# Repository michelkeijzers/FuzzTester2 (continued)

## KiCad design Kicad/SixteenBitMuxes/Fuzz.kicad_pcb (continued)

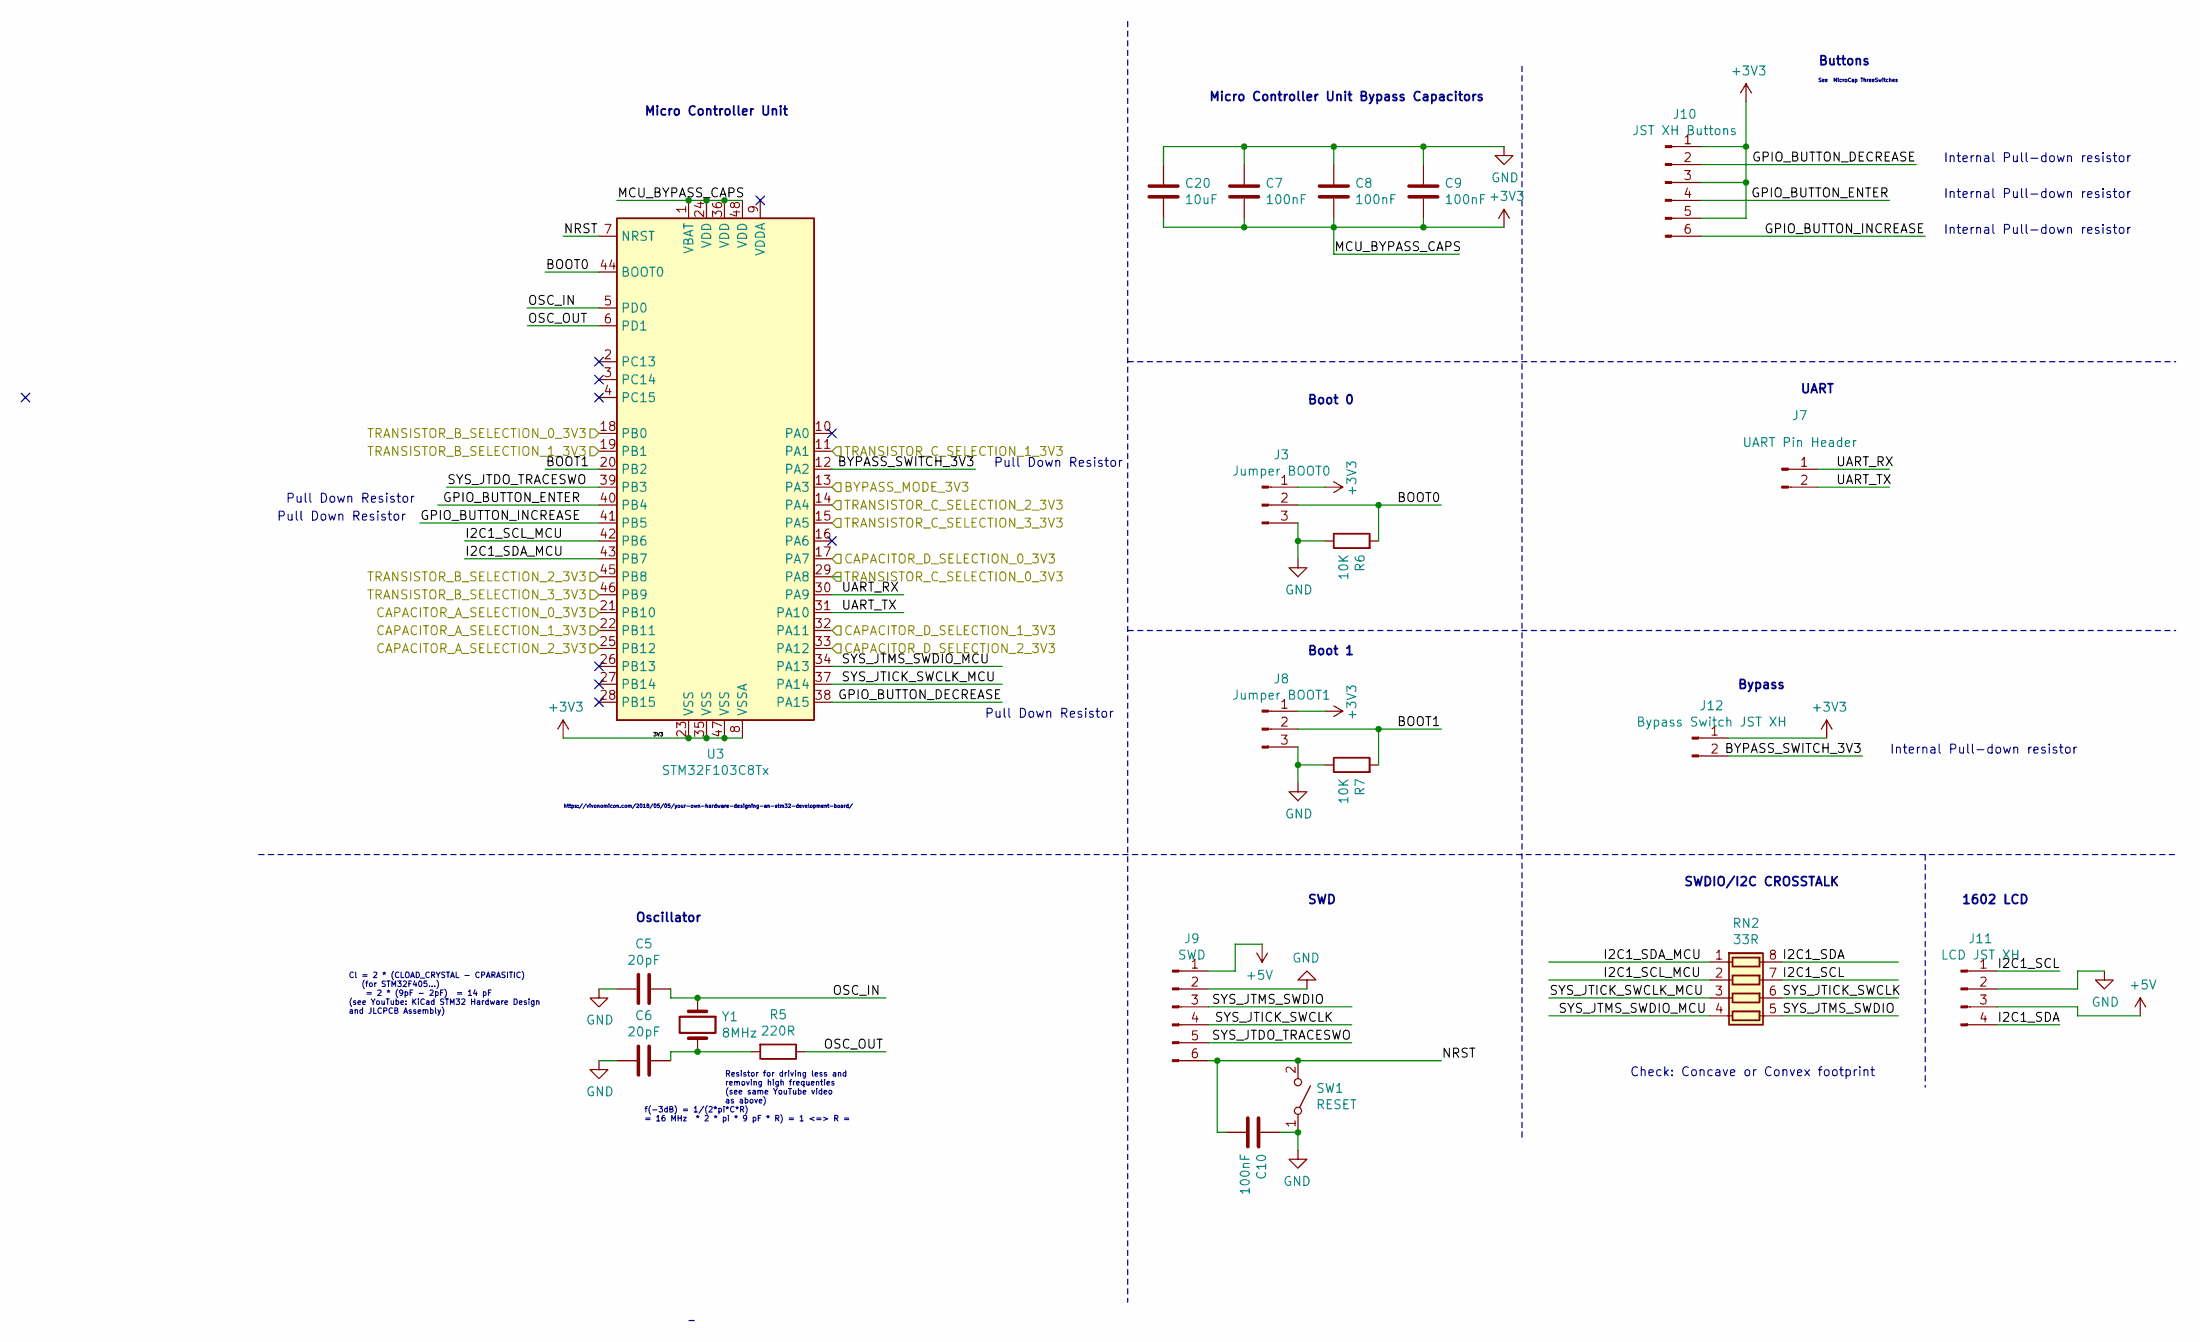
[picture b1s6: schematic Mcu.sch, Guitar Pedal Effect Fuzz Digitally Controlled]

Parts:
C5, C6: 20pF; C_0805_2012Metric_Pad1.15x1.40mm_HandSolder
C7, C8, C9, C10: 100nF; C_0805_2012Metric_Pad1.15x1.40mm_HandSolder
C20: 10uF; C_0805_2012Metric_Pad1.15x1.40mm_HandSolder
J3: Jumper BOOT0; PinHeader_1x03_P2.54mm_Vertical
J7: UART Pin Header; PinHeader_1x02_P2.54mm_Vertical
J8: Jumper BOOT1; PinHeader_1x03_P2.54mm_Vertical
J9: SWD; PinHeader_1x06_P2.54mm_Vertical
J10: JST XH Buttons; JST_XH_B6B-XH-A_1x06_P2.50mm_Vertical
J11: LCD JST XH; JST_XH_B4B-XH-A_1x04_P2.50mm_Vertical
J12: Bypass Switch JST XH; JST_XH_B2B-XH-A_1x02_P2.50mm_Vertical
R5: 220R; R_0805_2012Metric_Pad1.15x1.40mm_HandSolder
R6, R7: 10K; R_0805_2012Metric_Pad1.15x1.40mm_HandSolder
RN2: 33R; R_Array_Convex_4x0603
SW1: RESET; SW_SPST_CK_RS282G05A3
U3: STM32F103C8Tx; LQFP-48_7x7mm_P0.5mm
Y1: 8MHz; Crystal_HC49-4H_Vertical

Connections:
+3V3: C7.2, C8.2, C9.2, C20.2, J3.1, J8.1, J10.1, J10.3, J10.5, J12.1, U3.1 (VBAT), U3.8 (VSSA), U3.23 (VSS), U3.24 (VDD), U3.35 (VSS), U3.36 (VDD), U3.47 (VSS), U3.48 (VDD); also elsewhere on the board
+5V: J9.1, J11.3; also elsewhere on the board
/BYPASS_MODE_3V3: U3.13 (PA3); also elsewhere on the board
/CAPACITOR_A_SELECTION_0_3V3: U3.21 (PB10); also elsewhere on the board
/CAPACITOR_A_SELECTION_1_3V3: U3.22 (PB11); also elsewhere on the board
/CAPACITOR_A_SELECTION_2_3V3: U3.25 (PB12); also elsewhere on the board
/CAPACITOR_D_SELECTION_0_3V3: U3.17 (PA7); also elsewhere on the board
/CAPACITOR_D_SELECTION_1_3V3: U3.32 (PA11); also elsewhere on the board
/CAPACITOR_D_SELECTION_2_3V3: U3.33 (PA12); also elsewhere on the board
/Mcu/BOOT0: J3.2, R6.2, U3.44 (BOOT0)
/Mcu/BOOT1: J8.2, R7.2, U3.20 (PB2)
/Mcu/BYPASS_SWITCH_3V3: J12.2, U3.12 (PA2)
/Mcu/GPIO_BUTTON_DECREASE: J10.2, U3.38 (PA15)
/Mcu/GPIO_BUTTON_ENTER: J10.4, U3.40 (PB4)
/Mcu/GPIO_BUTTON_INCREASE: J10.6, U3.41 (PB5)
/Mcu/I2C1_SCL: J11.1, RN2.7 (R2.2)
/Mcu/I2C1_SCL_MCU: RN2.2 (R2.1), U3.42 (PB6)
/Mcu/I2C1_SDA: J11.4, RN2.8 (R1.2)
/Mcu/I2C1_SDA_MCU: RN2.1 (R1.1), U3.43 (PB7)
/Mcu/NRST: C10.1, J9.6, SW1.2 (B), U3.7 (NRST)
/Mcu/OSC_IN: C5.1, U3.5 (PD0), Y1.1
/Mcu/OSC_OUT: R5.1, U3.6 (PD1)
/Mcu/SYS_JTDO_TRACESWO: J9.5, U3.39 (PB3)
/Mcu/SYS_JTICK_SWCLK: J9.4, RN2.6 (R3.2)
/Mcu/SYS_JTICK_SWCLK_MCU: RN2.3 (R3.1), U3.37 (PA14)
/Mcu/SYS_JTMS_SWDIO: J9.3, RN2.5 (R4.2)
/Mcu/SYS_JTMS_SWDIO_MCU: RN2.4 (R4.1), U3.34 (PA13)
/Mcu/UART_RX: J7.1, U3.30 (PA9)
/Mcu/UART_TX: J7.2, U3.31 (PA10)
/TRANSISTOR_B_SELECTION_0_3V3: U3.18 (PB0); also elsewhere on the board
/TRANSISTOR_B_SELECTION_1_3V3: U3.19 (PB1); also elsewhere on the board
/TRANSISTOR_B_SELECTION_2_3V3: U3.45 (PB8); also elsewhere on the board
/TRANSISTOR_B_SELECTION_3_3V3: U3.46 (PB9); also elsewhere on the board
/TRANSISTOR_C_SELECTION_0_3V3: U3.29 (PA8); also elsewhere on the board
/TRANSISTOR_C_SELECTION_1_3V3: U3.11 (PA1); also elsewhere on the board
/TRANSISTOR_C_SELECTION_2_3V3: U3.14 (PA4); also elsewhere on the board
/TRANSISTOR_C_SELECTION_3_3V3: U3.15 (PA5); also elsewhere on the board
GND: C5.2, C6.2, C7.1, C8.1, C9.1, C10.2, C20.1, J3.3, J8.3, J9.2, J11.2, R6.1, R7.1, SW1.1 (A); also elsewhere on the board
unnamed: C6.1, R5.2, Y1.2

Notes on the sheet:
Micro Controller Unit Bypass Capacitors
https://vivonomicon.com/2018/05/05/your-own-hardware-designing-an-stm32-development-board/
Boot 0
1602 LCD
Pull Down Resistor
SWDIO/I2C CROSSTALK
Check: Concave or Convex footprint
Bypass
See MicroCap ThreeSwitches
Buttons
Internal Pull-down resistor
Cl = 2 * (CLOAD_CRYSTAL - CPARASITIC) (for STM32F405...) = 2 * (9pF - 2pF) = 14 pF (see YouTube: KiCad STM32 Hardware Design and JLCPCB Assembly)
Resistor for driving less and removing high frequenties (see same YouTube video as above)
f(-3dB) = 1/(2*pi*C*R) = 16 MHz * 2 * pi * 9 pF * R) = 1 <=> R =
Oscillator
Micro Controller Unit
Boot 1
SWD
UART

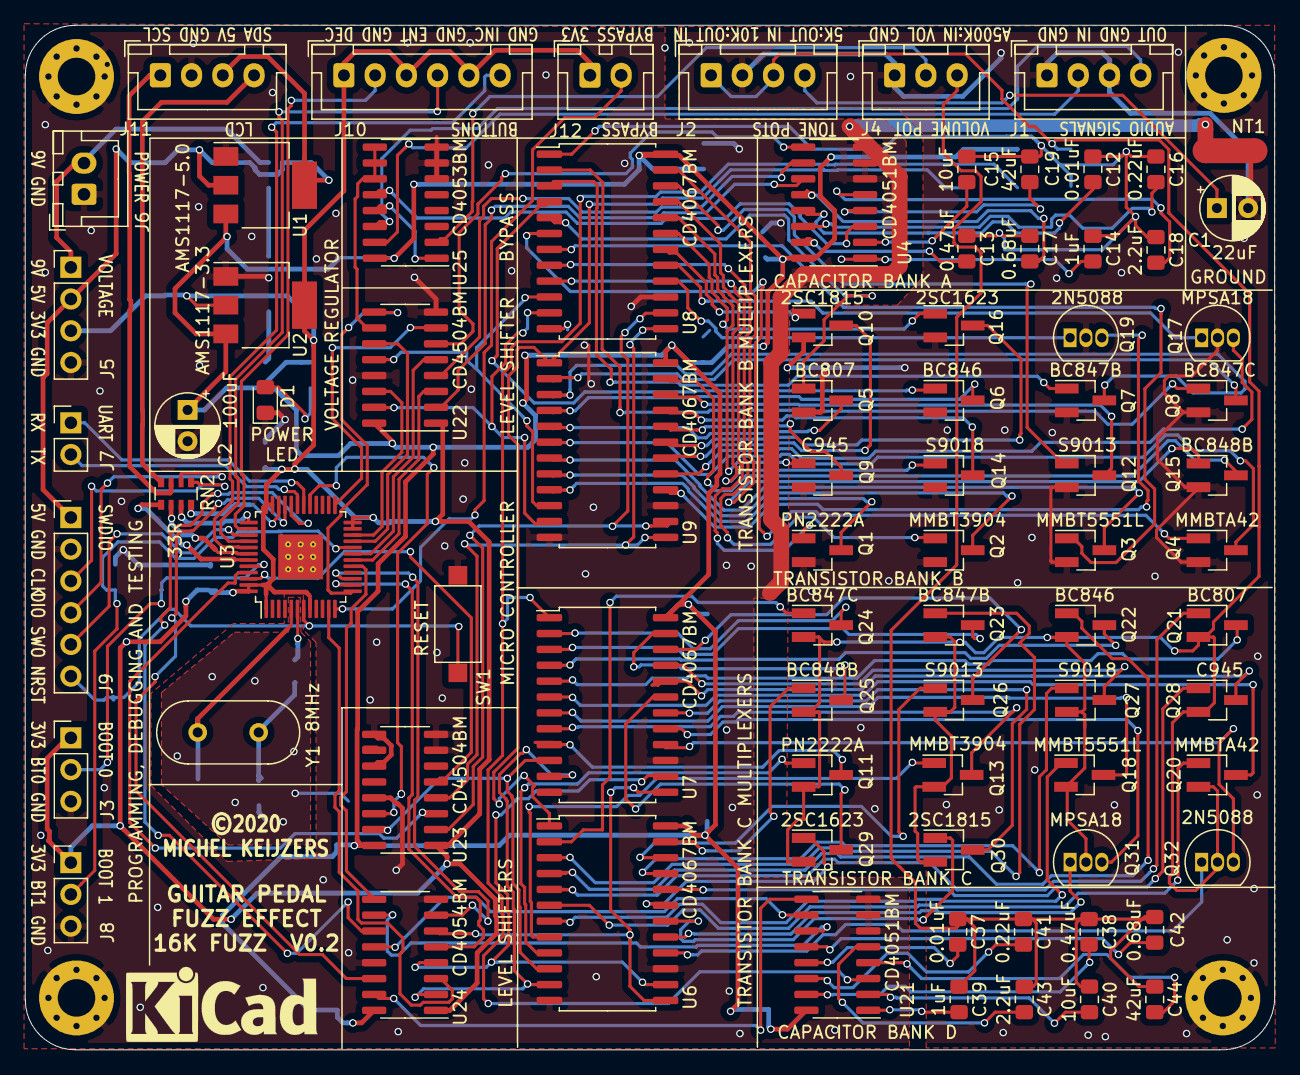
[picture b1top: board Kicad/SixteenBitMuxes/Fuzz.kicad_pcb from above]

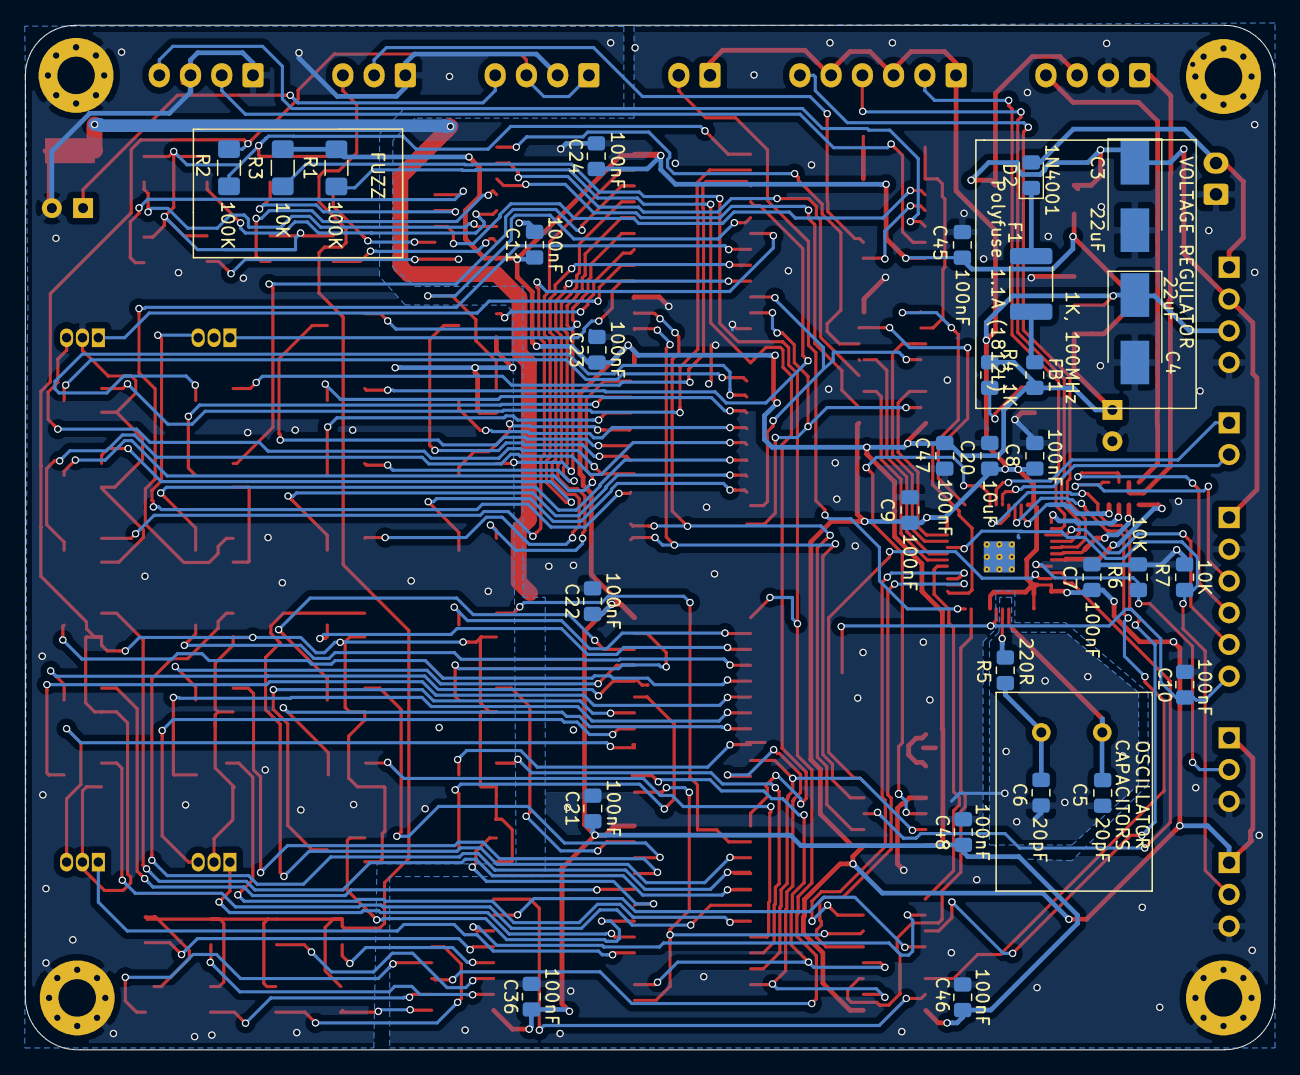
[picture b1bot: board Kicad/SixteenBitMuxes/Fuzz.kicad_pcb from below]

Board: 2 copper layers, 100.0 x 82.0 mm, 113 parts (29 on the bottom side), 151 nets.

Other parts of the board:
Q21: BC807; SOT-23_Handsoldering
Q22: BC846; SOT-23_Handsoldering
Q23: BC847B; SOT-23_Handsoldering
Q29: 2SC1623; SOT-23_Handsoldering
Q32: 2N5088; TO-92_Inline
U21: CD4051BM; SOIC-16_3.9x9.9mm_P1.27mm

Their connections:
/+9V_SAFE: U21.16; also elsewhere on the board
/B10K: Q21.2, Q22.2, Q23.2, Q29.2, Q32.2; also elsewhere on the board
/CAPACITOR_D_SELECTION_0: U21.11; also elsewhere on the board
/CAPACITOR_D_SELECTION_1: U21.10; also elsewhere on the board
/CAPACITOR_D_SELECTION_2: U21.9; also elsewhere on the board
/CapacitorsD/CAPACITOR_AUDIO_INPUT: U21.3; also elsewhere on the board
/TransistorsC/5_BASE: Q21.1; also elsewhere on the board
/TransistorsC/5_COLLECTOR: Q21.3; also elsewhere on the board
/TransistorsC/6_BASE: Q22.1; also elsewhere on the board
/TransistorsC/6_COLLECTOR: Q22.3; also elsewhere on the board
/TransistorsC/7_BASE: Q23.1; also elsewhere on the board
/TransistorsC/7_COLLECTOR: Q23.3; also elsewhere on the board
/TransistorsC/13_BASE: Q29.1; also elsewhere on the board
/TransistorsC/13_COLLECTOR: Q29.3; also elsewhere on the board
/TransistorsC/16_BASE: Q32.1; also elsewhere on the board
/TransistorsC/16_COLLECTOR: Q32.3; also elsewhere on the board
GND: U21.6, U21.7, U21.8; also elsewhere on the board
unnamed 139: U21.13; also elsewhere on the board
unnamed 140: U21.15; also elsewhere on the board
unnamed 141: U21.1; also elsewhere on the board
unnamed 142: U21.2; also elsewhere on the board
unnamed 143: U21.14; also elsewhere on the board
unnamed 144: U21.12; also elsewhere on the board
unnamed 145: U21.5; also elsewhere on the board
unnamed 146: U21.4; also elsewhere on the board

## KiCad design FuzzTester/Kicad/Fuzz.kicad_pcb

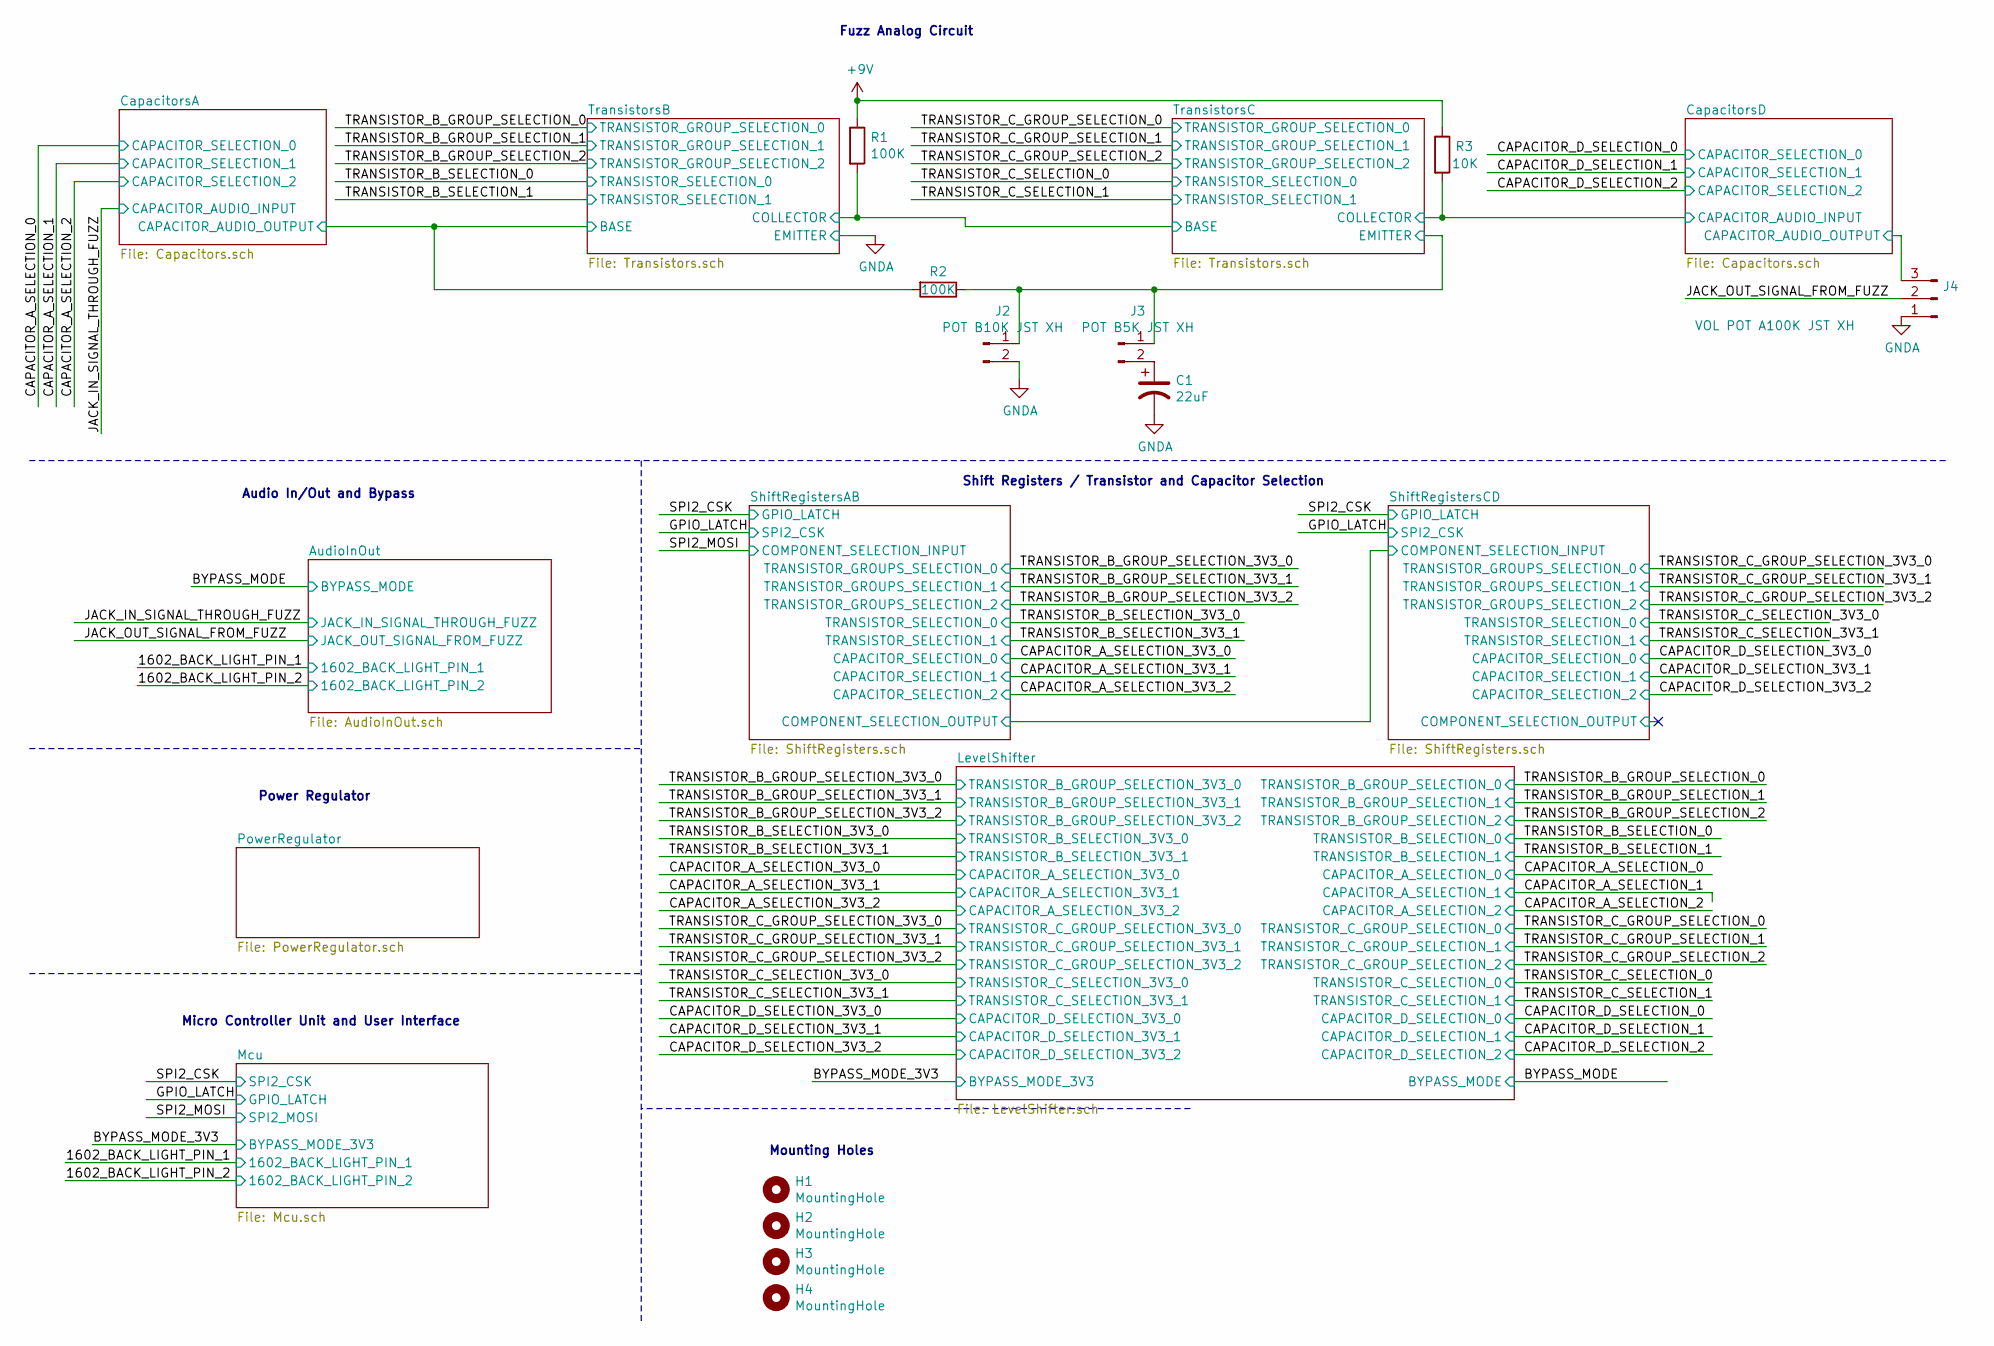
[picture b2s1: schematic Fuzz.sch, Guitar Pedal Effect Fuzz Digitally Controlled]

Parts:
C1: 22uF; CP_Radial_D5.0mm_P2.50mm
H1, H2, H3, H4: MountingHole; MountingHole_3.2mm_M3
J2: POT B10K JST XH; JST_XH_B2B-XH-A_1x02_P2.50mm_Vertical
J3: POT B5K JST XH; JST_XH_B2B-XH-A_1x02_P2.50mm_Vertical
J4: VOL POT A100K JST XH; JST_XH_B3B-XH-A_1x03_P2.50mm_Vertical
R1, R2: 100K; R_1206_3216Metric_Pad1.42x1.75mm_HandSolder
R3: 10K; R_1206_3216Metric_Pad1.42x1.75mm_HandSolder

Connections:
+9V: R1.1, R3.1; also elsewhere on the board
/CapacitorsD/CAPACITOR_AUDIO_INPUT: R3.2; also elsewhere on the board
/CapacitorsD/CAPACITOR_AUDIO_OUTPUT: J4.3; also elsewhere on the board
/JACK_OUT_SIGNAL_FROM_FUZZ: J4.2; also elsewhere on the board
/TransistorsB/BASE: R2.2; also elsewhere on the board
/TransistorsC/BASE: R1.2; also elsewhere on the board
/TransistorsC/EMITTER: J2.1, J3.1, R2.1; also elsewhere on the board
GNDA: C1.2, J2.2, J4.1; also elsewhere on the board
unnamed: C1.1, J3.2

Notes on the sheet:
Fuzz Analog Circuit
Audio In/Out and Bypass
Shift Registers / Transistor and Capacitor Selection
Power Regulator
Micro Controller Unit and User Interface
Mounting Holes

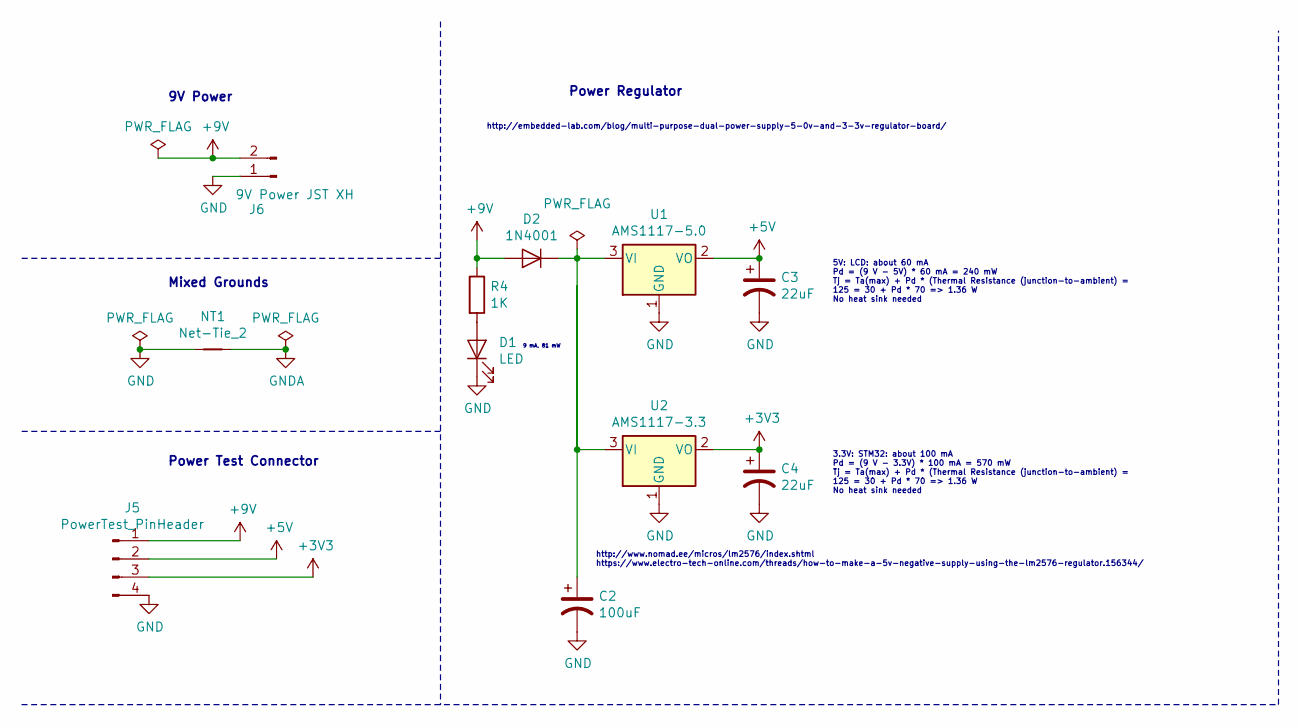
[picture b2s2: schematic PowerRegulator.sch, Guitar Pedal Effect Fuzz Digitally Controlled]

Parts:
C2: 100uF; CP_Radial_D5.0mm_P2.50mm
C3, C4: 22uF; CP_Radial_D5.0mm_P2.50mm
D1: LED; LED_0805_2012Metric_Pad1.15x1.40mm_HandSolder
D2: 1N4001; D_0805_2012Metric_Pad1.15x1.40mm_HandSolder
J5: PowerTest_PinHeader; PinHeader_1x04_P2.54mm_Vertical
J6: 9V Power JST XH; JST_XH_B2B-XH-A_1x02_P2.50mm_Vertical
NT1: Net-Tie_2; NetTie-2_SMD_Pad2.0mm
R4: 1K; R_0805_2012Metric_Pad1.15x1.40mm_HandSolder
U1: AMS1117-5.0; SOT-223-3_TabPin2
U2: AMS1117-3.3; SOT-223-3_TabPin2

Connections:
+3V3: C4.1, J5.3, U2.2 (VO); also elsewhere on the board
+5V: C3.1, J5.2, U1.2 (VO); also elsewhere on the board
+9V: D2.2 (A), J5.1, J6.2, R4.1; also elsewhere on the board
GND: C2.2, C3.2, C4.2, D1.1 (K), J5.4, J6.1, NT1.1, U1.1 (GND), U2.1 (GND); also elsewhere on the board
GNDA: NT1.2; also elsewhere on the board
unnamed: C2.1, D2.1 (K), U1.3 (VI), U2.3 (VI)
unnamed: D1.2 (A), R4.2

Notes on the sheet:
9V Power
9 mA, 81 mW
5V: LCD: about 60 mA Pd = (9 V - 5V) * 60 mA = 240 mW Tj = Ta(max) + Pd * (Thermal Resistance (junction-to-ambient) = 125 = 30 + Pd * 70 => 1.36 W No heat sink needed
3.3V: STM32: about 100 mA Pd = (9 V - 3.3V) * 100 mA = 570 mW Tj = Ta(max) + Pd * (Thermal Resistance (junction-to-ambient) = 125 = 30 + Pd * 70 => 1.36 W No heat sink needed
Power Regulator
http://embedded-lab.com/blog/multi-purpose-dual-power-supply-5-0v-and-3-3v-regulator-board/
https://www.electro-tech-online.com/threads/how-to-make-a-5v-negative-supply-using-the-lm2576-regulator.156344/
http://www.nomad.ee/micros/lm2576/index.shtml
Power Test Connector
Mixed Grounds

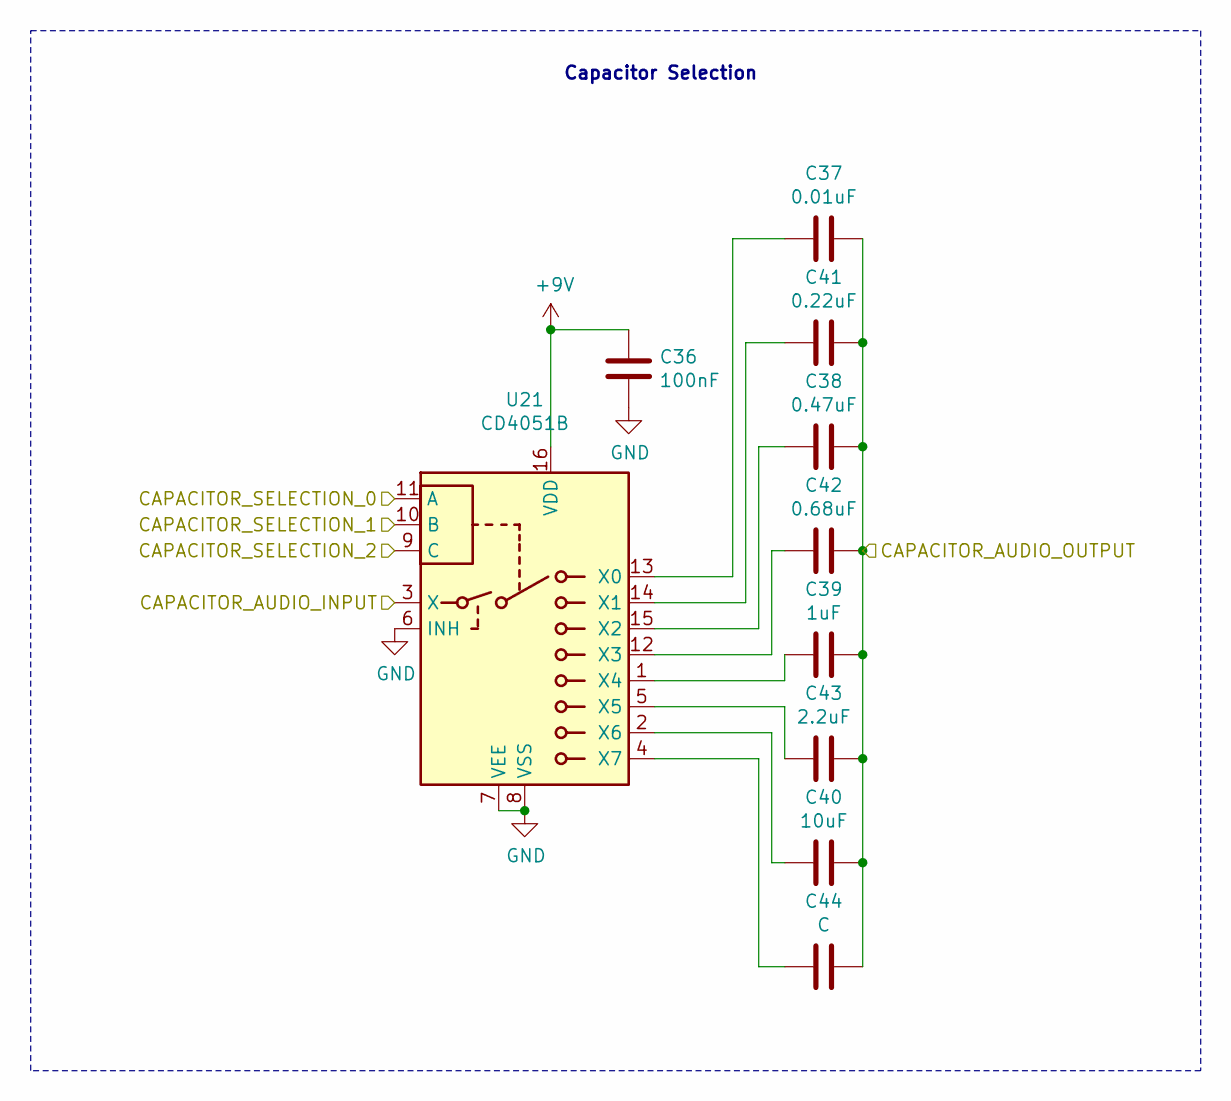
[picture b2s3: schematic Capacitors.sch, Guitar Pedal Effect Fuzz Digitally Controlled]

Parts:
C11: 100nF; C_0805_2012Metric_Pad1.15x1.40mm_HandSolder
C12: 0.01uF; C_0805_2012Metric_Pad1.15x1.40mm_HandSolder
C13: 0.47uF; C_0805_2012Metric_Pad1.15x1.40mm_HandSolder
C14: 1uF; C_0805_2012Metric_Pad1.15x1.40mm_HandSolder
C15: 10uF; C_0805_2012Metric_Pad1.15x1.40mm_HandSolder
C16: 0.22uF; C_0805_2012Metric_Pad1.15x1.40mm_HandSolder
C17: 0.68uF; C_0805_2012Metric_Pad1.15x1.40mm_HandSolder
C18: 2.2uF; C_0805_2012Metric_Pad1.15x1.40mm_HandSolder
C19: C; C_0805_2012Metric_Pad1.15x1.40mm_HandSolder
U4: CD4051B; SOIC-16_3.9x9.9mm_P1.27mm

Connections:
+9V: C11.1, U4.16 (VDD); also elsewhere on the board
/CAPACITOR_A_SELECTION_0: U4.11 (A); also elsewhere on the board
/CAPACITOR_A_SELECTION_1: U4.10 (B); also elsewhere on the board
/CAPACITOR_A_SELECTION_2: U4.9 (C); also elsewhere on the board
/JACK_IN_SIGNAL_THROUGH_FUZZ: U4.3 (X); also elsewhere on the board
/TransistorsB/BASE: C12.1, C13.1, C14.1, C15.1, C16.1, C17.1, C18.1, C19.1; also elsewhere on the board
GND: C11.2, U4.6 (INH), U4.7 (VEE), U4.8 (VSS); also elsewhere on the board
unnamed: C12.2, U4.13 (X0)
unnamed: C13.2, U4.15 (X2)
unnamed: C14.2, U4.1 (X4)
unnamed: C15.2, U4.2 (X6)
unnamed: C16.2, U4.14 (X1)
unnamed: C17.2, U4.12 (X3)
unnamed: C18.2, U4.5 (X5)
unnamed: C19.2, U4.4 (X7)

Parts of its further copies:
C36: 100nF; C_0805_2012Metric_Pad1.15x1.40mm_HandSolder
C37: 0.01uF; C_0805_2012Metric_Pad1.15x1.40mm_HandSolder
C38: 0.47uF; C_0805_2012Metric_Pad1.15x1.40mm_HandSolder
C39: 1uF; C_0805_2012Metric_Pad1.15x1.40mm_HandSolder
C40: 10uF; C_0805_2012Metric_Pad1.15x1.40mm_HandSolder
C41: 0.22uF; C_0805_2012Metric_Pad1.15x1.40mm_HandSolder
C42: 0.68uF; C_0805_2012Metric_Pad1.15x1.40mm_HandSolder
C43: 2.2uF; C_0805_2012Metric_Pad1.15x1.40mm_HandSolder
C44: C; C_0805_2012Metric_Pad1.15x1.40mm_HandSolder
U21: CD4051B; SOIC-16_3.9x9.9mm_P1.27mm

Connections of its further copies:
+9V: C36.1, U21.16 (VDD); also elsewhere on the board
/CAPACITOR_D_SELECTION_0: U21.11 (A); also elsewhere on the board
/CAPACITOR_D_SELECTION_1: U21.10 (B); also elsewhere on the board
/CAPACITOR_D_SELECTION_2: U21.9 (C); also elsewhere on the board
/CapacitorsD/CAPACITOR_AUDIO_INPUT: U21.3 (X); also elsewhere on the board
/CapacitorsD/CAPACITOR_AUDIO_OUTPUT: C37.1, C38.1, C39.1, C40.1, C41.1, C42.1, C43.1, C44.1; also elsewhere on the board
GND: C36.2, U21.6 (INH), U21.7 (VEE), U21.8 (VSS); also elsewhere on the board
unnamed: C37.2, U21.13 (X0)
unnamed: C38.2, U21.15 (X2)
unnamed: C39.2, U21.1 (X4)
unnamed: C40.2, U21.2 (X6)
unnamed: C41.2, U21.14 (X1)
unnamed: C42.2, U21.12 (X3)
unnamed: C43.2, U21.5 (X5)
unnamed: C44.2, U21.4 (X7)

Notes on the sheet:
Capacitor Selection

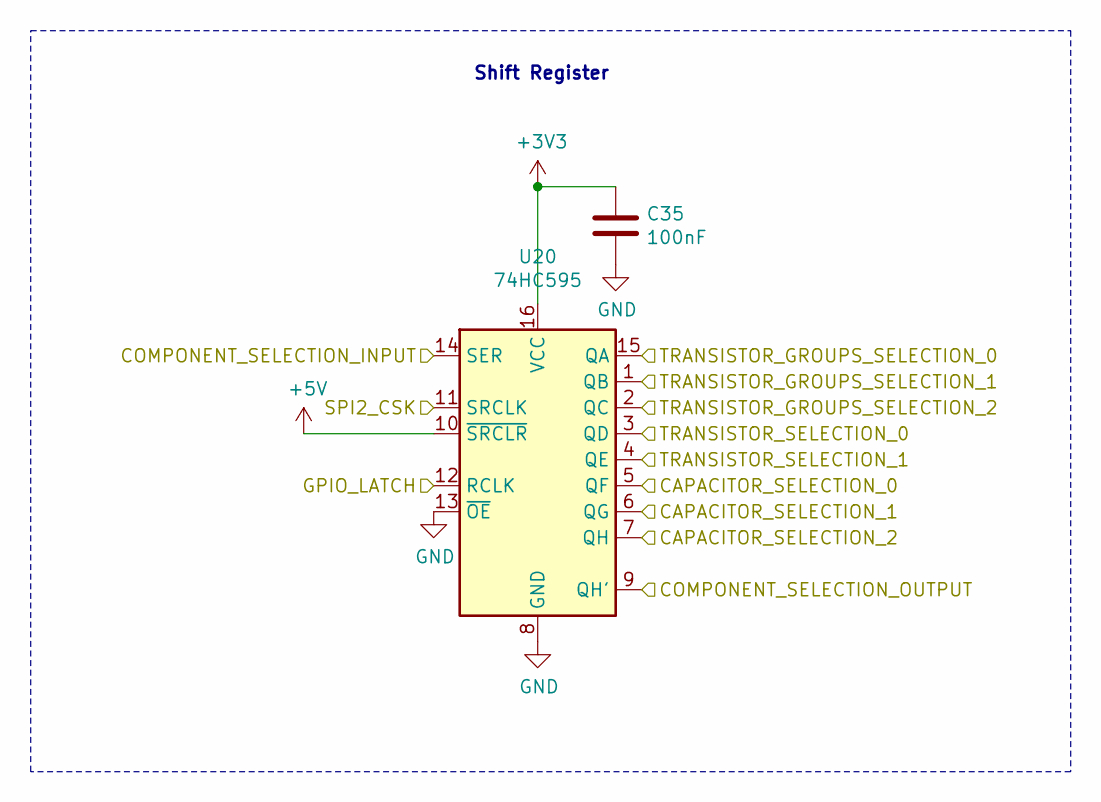
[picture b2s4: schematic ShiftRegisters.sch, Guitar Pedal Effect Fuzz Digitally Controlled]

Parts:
C20: 100nF; C_0805_2012Metric_Pad1.15x1.40mm_HandSolder
U5: 74HC595; SOIC-16_3.9x9.9mm_P1.27mm

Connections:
+3V3: C20.1, U5.16 (VCC); also elsewhere on the board
+5V: U5.10 (~SRCLR); also elsewhere on the board
/CAPACITOR_A_SELECTION_3V3_0: U5.5 (QF); also elsewhere on the board
/CAPACITOR_A_SELECTION_3V3_1: U5.6 (QG); also elsewhere on the board
/CAPACITOR_A_SELECTION_3V3_2: U5.7 (QH); also elsewhere on the board
/ShiftRegistersCD/COMPONENT_SELECTION_INPUT: U5.9 (QH'); also elsewhere on the board
/TRANSISTOR_B_GROUP_SELECTION_3V3_0: U5.15 (QA); also elsewhere on the board
/TRANSISTOR_B_GROUP_SELECTION_3V3_1: U5.1 (QB); also elsewhere on the board
/TRANSISTOR_B_GROUP_SELECTION_3V3_2: U5.2 (QC); also elsewhere on the board
/TRANSISTOR_B_SELECTION_3V3_0: U5.3 (QD); also elsewhere on the board
/TRANSISTOR_B_SELECTION_3V3_1: U5.4 (QE); also elsewhere on the board
GND: C20.2, U5.8 (GND), U5.13 (~OE); also elsewhere on the board

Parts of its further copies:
C35: 100nF; C_0805_2012Metric_Pad1.15x1.40mm_HandSolder
U20: 74HC595; SOIC-16_3.9x9.9mm_P1.27mm

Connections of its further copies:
+3V3: C35.1, U20.16 (VCC); also elsewhere on the board
+5V: U20.10 (~SRCLR); also elsewhere on the board
/CAPACITOR_D_SELECTION_3V3_0: U20.5 (QF); also elsewhere on the board
/CAPACITOR_D_SELECTION_3V3_1: U20.6 (QG); also elsewhere on the board
/CAPACITOR_D_SELECTION_3V3_2: U20.7 (QH); also elsewhere on the board
/ShiftRegistersCD/COMPONENT_SELECTION_INPUT: U20.14 (SER); also elsewhere on the board
/ShiftRegistersCD/COMPONENT_SELECTION_OUTPUT: U20.9 (QH')
/TRANSISTOR_C_GROUP_SELECTION_3V3_0: U20.15 (QA); also elsewhere on the board
/TRANSISTOR_C_GROUP_SELECTION_3V3_1: U20.1 (QB); also elsewhere on the board
/TRANSISTOR_C_GROUP_SELECTION_3V3_2: U20.2 (QC); also elsewhere on the board
/TRANSISTOR_C_SELECTION_3V3_0: U20.3 (QD); also elsewhere on the board
/TRANSISTOR_C_SELECTION_3V3_1: U20.4 (QE); also elsewhere on the board
GND: C35.2, U20.8 (GND), U20.13 (~OE); also elsewhere on the board

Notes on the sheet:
Shift Register
